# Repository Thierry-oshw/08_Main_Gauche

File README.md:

# 08_Main_Gauche
 Clavier et joystick main gauche

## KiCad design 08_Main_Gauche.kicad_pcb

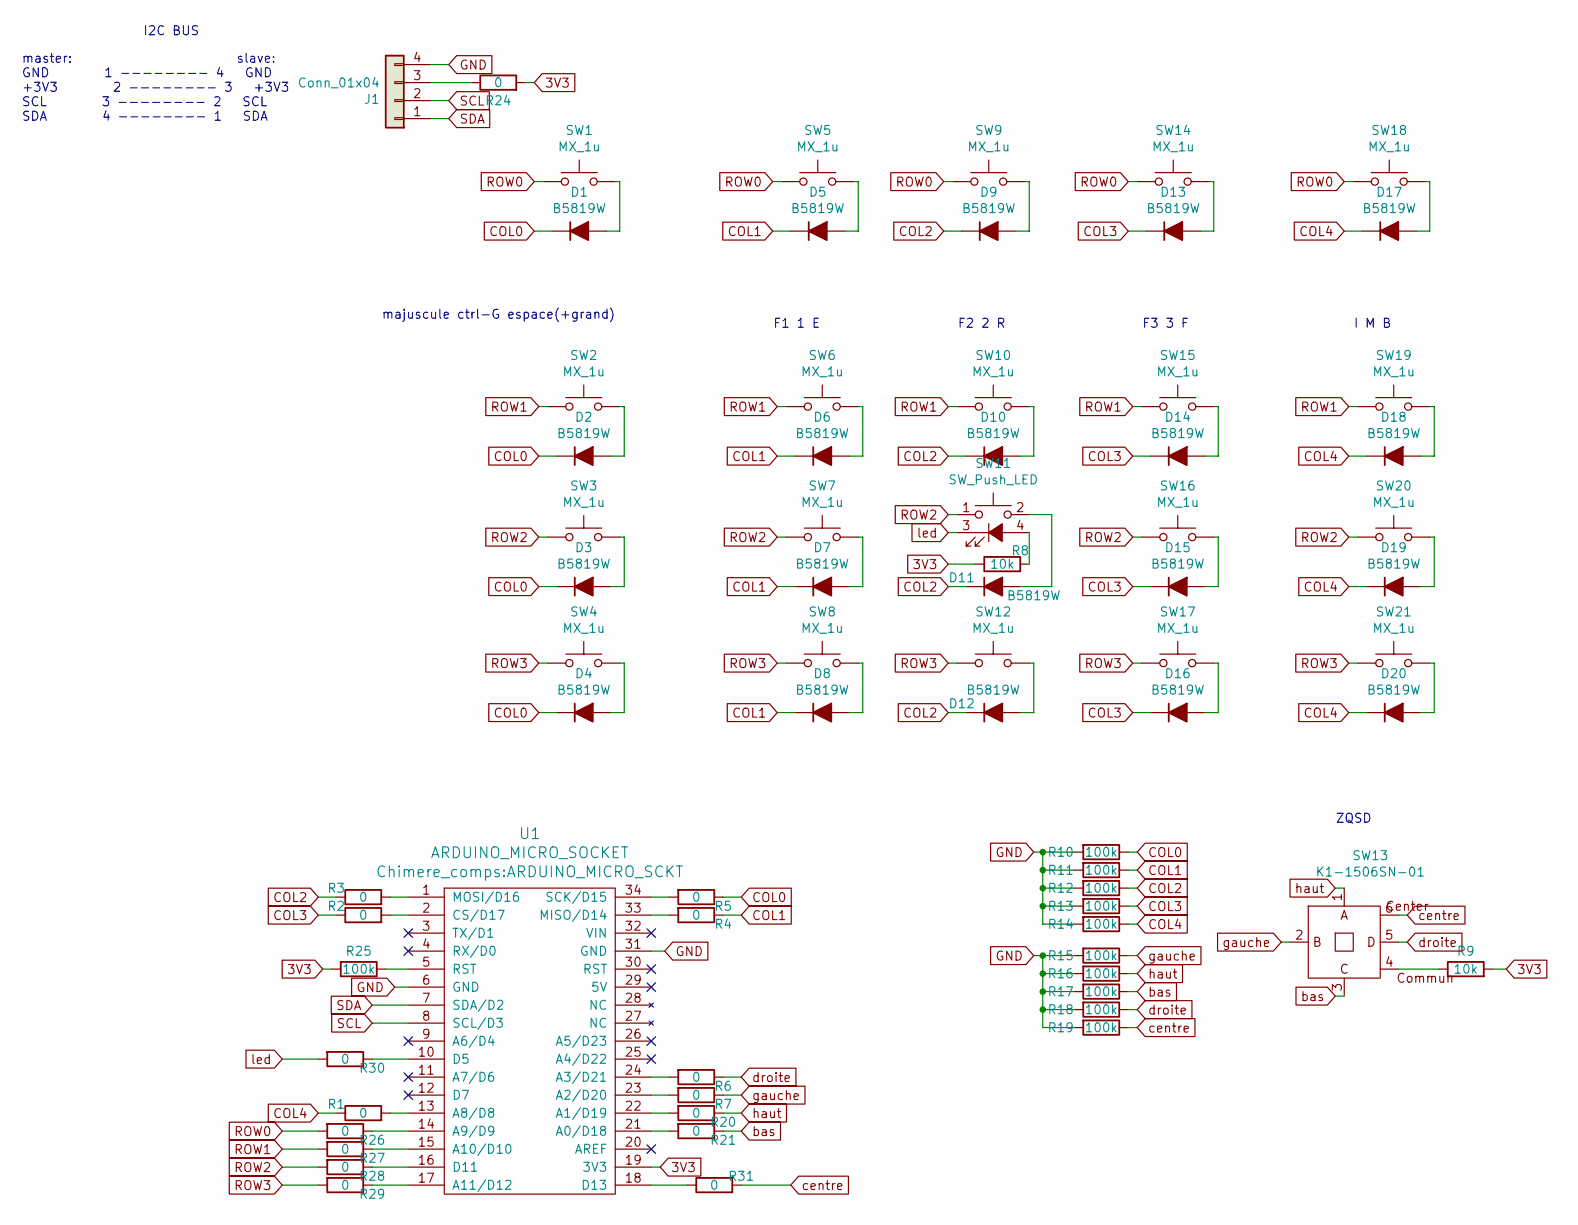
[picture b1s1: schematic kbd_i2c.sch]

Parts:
D1, D2, D3, D4, D5, D6, D7, D8, D9, D10, D11, D12, D13, D14, D15, D16, D17, D18, D19, D20: B5819W; D_SOD-123
J1: Conn_01x04; JST_XH_B4B-XH-A_1x04_P2.50mm_Vertical
R1, R2, R3, R4, R5, R6, R7, R20, R21, R24, R26, R27, R28, R29, R30, R31: 0; R_0603_1608Metric
R8, R9: 10k; R_0603_1608Metric
R10, R11, R12, R13, R14, R15, R16, R17, R18, R19, R25: 100k; R_0603_1608Metric
SW1, SW2, SW3, SW4, SW5, SW6, SW7, SW8, SW9, SW10, SW12, SW14, SW15, SW16, SW17, SW18, SW19, SW20, SW21: MX_1u; SW_Cherry_MX_1.00u_PCB
SW11: SW_Push_LED; SW_MX_LED
SW13: K1-1506SN-01
U1: ARDUINO_MICRO_SOCKET; ARDUINO_MICRO_SCKT

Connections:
3V3: R8.1, R9.2, R24.2, R25.2, U1.19 (3V3)
COL0: D1.1 (K), D2.1 (K), D3.1 (K), D4.1 (K), R5.1, R10.1
COL1: D5.1 (K), D6.1 (K), D7.1 (K), D8.1 (K), R4.1, R11.1
COL2: D9.1 (K), D10.1 (K), D11.1 (K), D12.1 (K), R3.1, R12.1
COL3: D13.1 (K), D14.1 (K), D15.1 (K), D16.1 (K), R2.1, R13.1
COL4: D17.1 (K), D18.1 (K), D19.1 (K), D20.1 (K), R1.1, R14.1
GND: J1.4, R10.2, R11.2, R12.2, R13.2, R14.2, R15.2, R16.2, R17.2, R18.2, R19.2, U1.6 (GND), U1.31 (GND); also elsewhere on the board
unnamed: D1.2 (A), SW1.2
unnamed: D2.2 (A), SW2.2
unnamed: D3.2 (A), SW3.2
unnamed: D4.2 (A), SW4.2
unnamed: D5.2 (A), SW5.2
unnamed: D6.2 (A), SW6.2
unnamed: D7.2 (A), SW7.2
unnamed: D8.2 (A), SW8.2
unnamed: D9.2 (A), SW9.2
unnamed: D10.2 (A), SW10.2
unnamed: D11.2 (A), SW11.2
unnamed: D12.2 (A), SW12.2
unnamed: D13.2 (A), SW14.2
unnamed: D14.2 (A), SW15.2
unnamed: D15.2 (A), SW16.2
unnamed: D16.2 (A), SW17.2
unnamed: D17.2 (A), SW18.2
unnamed: D18.2 (A), SW19.2
unnamed: D19.2 (A), SW20.2
unnamed: D20.2 (A), SW21.2
unnamed: J1.3, R24.1
unnamed: R1.2, U1.13 (A8/D8)
unnamed: R2.2, U1.2 (CS/D17)
unnamed: R3.2, U1.1 (MOSI/D16)
unnamed: R4.2, U1.33 (MISO/D14)
unnamed: R5.2, U1.34 (SCK/D15)
unnamed: R6.2, U1.24 (A3/D21)
unnamed: R7.2, U1.23 (A2/D20)
unnamed: R8.2, SW11.4 (A)
unnamed: R9.1, SW13.4
unnamed: R20.2, U1.22 (A1/D19)
unnamed: R21.2, U1.21 (A0/D18)
unnamed: R25.1, U1.5 (RST)
unnamed: R26.1, U1.14 (A9/D9)
unnamed: R27.1, U1.15 (A10/D10)
unnamed: R28.1, U1.16 (D11)
unnamed: R29.1, U1.17 (A11/D12)
unnamed: R30.1, U1.10 (D5)
unnamed: R31.1, U1.18 (D13)
ROW0: R26.2, SW1.1, SW5.1, SW9.1, SW14.1, SW18.1
ROW1: R27.2, SW2.1, SW6.1, SW10.1, SW15.1, SW19.1
ROW2: R28.2, SW3.1, SW7.1, SW11.1, SW16.1, SW20.1
ROW3: R29.2, SW4.1, SW8.1, SW12.1, SW17.1, SW21.1
SCL: J1.2, U1.8 (SCL/D3)
SDA: J1.1, U1.7 (SDA/D2)
bas: R17.1, R21.1, SW13.3
centre: R19.1, R31.2, SW13.6
droite: R6.1, R18.1, SW13.5
gauche: R7.1, R15.1, SW13.2
haut: R16.1, R20.1, SW13.1
led: R30.2, SW11.3 (K)

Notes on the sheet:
ZQSD
F1 1 E
F2 2 R
F3 3 F
majuscule ctrl-G espace(+grand)
I M B
master: slave: GND 1 -------- 4 GND +3V3 2 -------- 3 +3V3 SCL 3 -------- 2 SCL SDA 4 -------- 1 SDA
I2C BUS

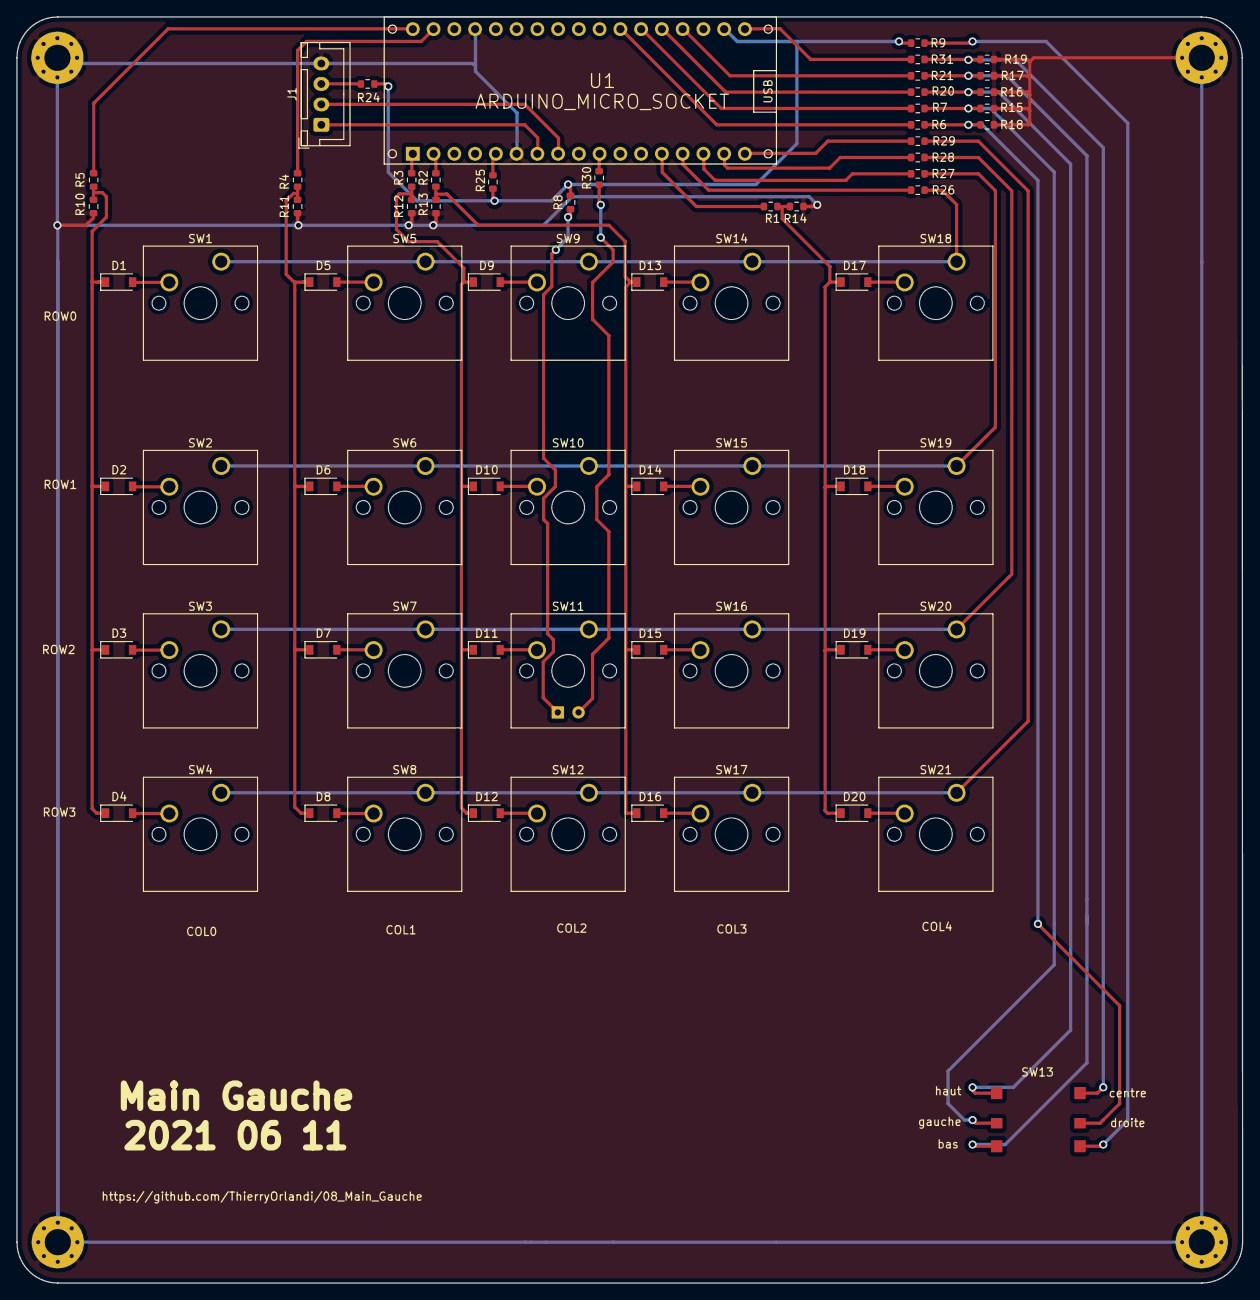
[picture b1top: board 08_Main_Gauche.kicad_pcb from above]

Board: 2 copper layers, 150.0 x 154.9 mm, 76 parts (0 on the bottom side), 58 nets.

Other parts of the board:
H1, H2, H3, H4: MountingHole_Pad; MountingHole_3.2mm_M3_Pad_Via

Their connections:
GND: H1.1, H2.1, H3.1, H4.1; also elsewhere on the board

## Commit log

2021-04-11 schema + placement + routage
2021-04-12 correction empreinte et routage; utilisation empreinte cherry mx led
2021-06-10 schema + routage
    - redistribution des touches
    - ajout 5ways switch
    - supprimé les empreintes pcb de touches résistives
2021-06-10 5ways switch mis en CMS
2021-06-11 correction schema et routage
    changement symbole et empreinte de arduino micro socket
2021-07-24 maj split librairies
2023-05-02 chgt nom fichier licence
2024-04-27 fioritures
